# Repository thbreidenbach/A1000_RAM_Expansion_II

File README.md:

# A1000_RAM_Expansion_II
Modern Amiga 1000 Front Ram Expansion

This project is an effort to offer a modern appraoch to the Amiga 1000 front Ram Expansion.

The included PCB is untested as of now and will probably eithor not work or be subject to change after initial testing.
Thanks to Joachim Firnhaber for his help and good words (there's a lot of... potential), I would probably not have published the files without his okay.

I suggest Users wait until propper testing was done, before ordering boards.

Logic holds current **untested** code. Just like the PCB Design this is currently no more than a starting point or boilerplate. If you're adventurous and it works, leave me a message!!

**Back**

**Front**

The Board has Testpoints for RAM Glue-Logic so hopefully issues can be sorted out fast.
HTML BOM is included and should help sourcing parts. RAM should probably go with CY62128ELL Which is available in TSOP-32 Footprint at Reichelt at an extremely low price point. All Parts excluding the 60-Pin Connector are probably less than 20,-- EUR.

See License before ordering or going forward with this Design.

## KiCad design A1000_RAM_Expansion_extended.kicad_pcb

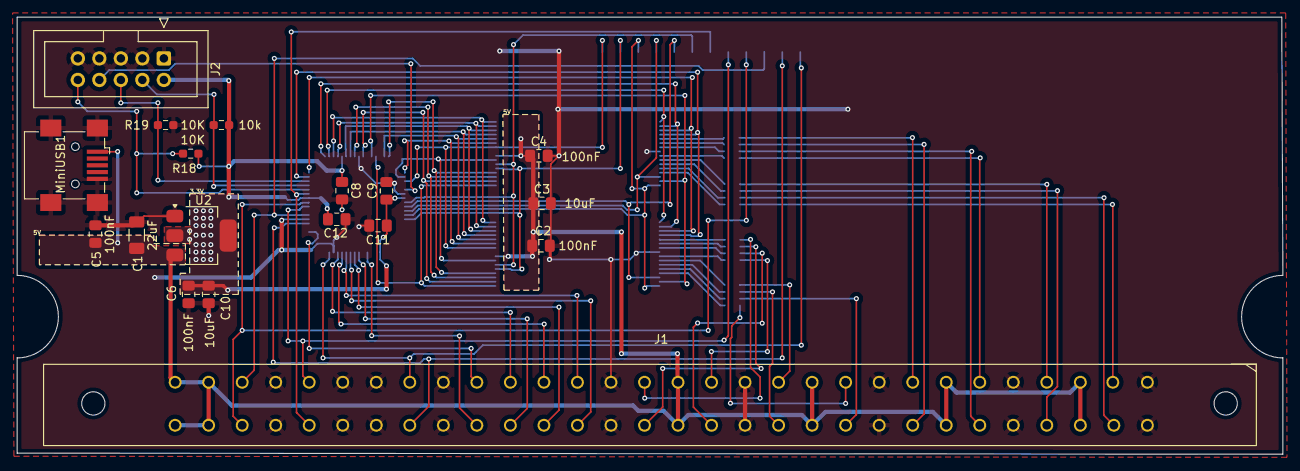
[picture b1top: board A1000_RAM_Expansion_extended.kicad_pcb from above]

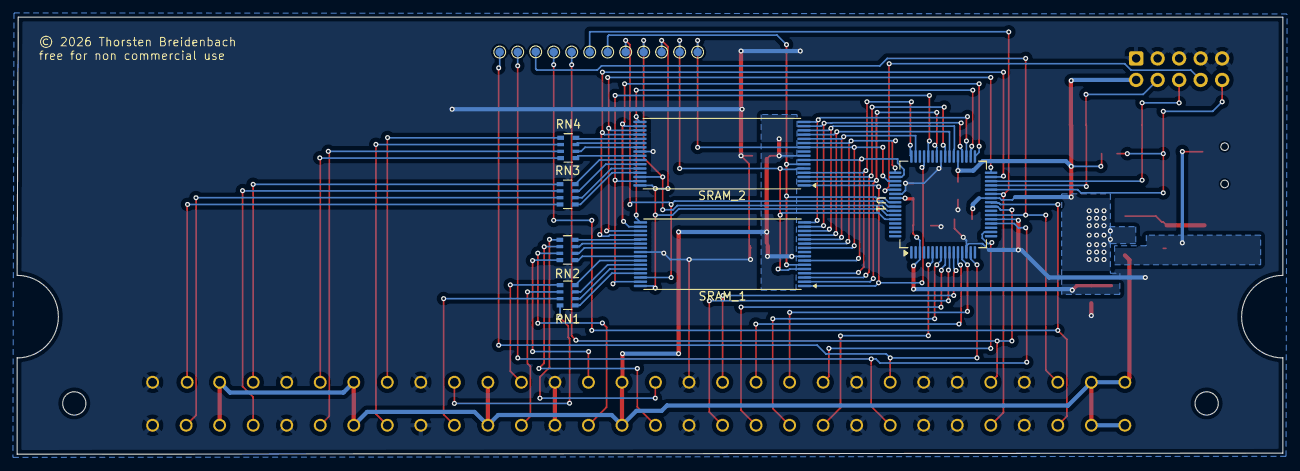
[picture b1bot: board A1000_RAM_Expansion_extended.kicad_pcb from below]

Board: 2 copper layers, 149.5 x 51.6 mm, 37 parts (19 on the bottom side), 75 nets.

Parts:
/casu_0, /casu_1: TestPoint_Pad_D1.0mm
/ce1_u: TestPoint_Pad_D1.0mm
/oe: TestPoint_Pad_D1.0mm
/ras: TestPoint_Pad_D1.0mm
/rrw: TestPoint_Pad_D1.0mm
/we: TestPoint_Pad_D1.0mm
C1: 22uF; C_1206_3216Metric_Pad1.33x1.80mm_HandSolder
C2, C5, C6, C8, C9, C11, C12: 100nF; C_0805_2012Metric_Pad1.18x1.45mm_HandSolder
C3, C10: 10uF; C_0805_2012Metric_Pad1.18x1.45mm_HandSolder
C4: C_Small; C_0805_2012Metric_Pad1.18x1.45mm_HandSolder
J1: Front_Connector; Connector_horizontal_amiga1.04_GREEN
J2: Conn_02x05_Odd_Even; IDC-Header_2x05_P2.54mm_Vertical
MiniUSB1: USB_Mini-B_Wuerth; USB_Mini-B_Wuerth_65100516121_Horizontal
R17: 10k; R_0603_1608Metric_Pad0.98x0.95mm_HandSolder
R18, R19: 10K; R_0603_1608Metric_Pad0.98x0.95mm_HandSolder
RN1, RN2, RN3, RN4: 33r; R_Array_Convex_4x0603
SRAM_1, SRAM_2: CY7C109D; TSOP-I-32_18.4x8mm_P0.5mm
U1: XC9572XL-xxVQx64; TQFP-64_10x10mm_P0.5mm
U2: LD1117S33TR_SOT223; SOT-223-3_TabPin2
casl0, casl1: TestPoint_Pad_D1.0mm
ce1_l, ce2: TestPoint_Pad_D1.0mm
sram_A16: TestPoint_Pad_D1.0mm

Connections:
+3.3V: C6.1, C8.1, C9.1, C10.1, C11.1, C12.1, J2.2, R17.2, R18.2, U1.3 (VCCINT), U1.26 (VCCIO), U1.37 (VCCINT), U1.55 (VCCIO), U2.2 (VO)
+5V: C1.1, C2.1, C3.1, C4.1, C5.1, J1.3, J1.7, J1.11, J1.15, J1.29, J1.30, J1.C (Pin_33), J1.H (Pin_37), J1.HH (Pin_59), J1.JJ (Pin_60), J1.M (Pin_41), J1.S (Pin_45), MiniUSB1.1 (VBUS), SRAM_1.8 (VCC), SRAM_2.8 (VCC), U2.3 (VI)
D0: J1.16, RN2.5 (R4.2)
D1: J1.T (Pin_46), RN2.6 (R3.2)
D2: J1.R (Pin_44), RN2.7 (R2.2)
D3: J1.14, RN2.8 (R1.2)
D4: J1.12, RN1.5 (R4.2)
D5: J1.N (Pin_42), RN1.6 (R3.2)
D6: J1.L (Pin_40), RN1.7 (R2.2)
D7: J1.10, RN1.8 (R1.2)
D8: J1.8, RN4.1 (R1.1)
D9: J1.J (Pin_38), RN4.2 (R2.1)
D10: J1.F (Pin_36), RN4.3 (R3.1)
D11: J1.6, RN4.4 (R4.1)
D12: J1.4, RN3.1 (R1.1)
D13: J1.D (Pin_34), RN3.2 (R2.1)
D14: J1.B (Pin_32), RN3.3 (R3.1)
D15: J1.2, RN3.4 (R4.1)
DRA0: J1.Y (Pin_51), U1.6 (I/O)
DRA1: J1.X (Pin_50), U1.8 (I/O)
DRA2: J1.W (Pin_49), U1.9 (I/O)
DRA3: J1.V (Pin_48), U1.10 (I/O)
DRA4: J1.18, U1.11 (I/O)
DRA5: J1.19, U1.12 (I/O)
DRA6: J1.20, U1.13 (I/O)
DRA7: J1.21, U1.18 (I/O)
GND: C1.2, C2.2, C3.2, C4.2, C5.2, C6.2, C8.2, C9.2, C10.2, C11.2, C12.2, J1.1, J1.5, J1.9, J1.13, J1.17, J1.22, J1.24, J1.25, J1.27, J1.A (Pin_31), J1.BB (Pin_54), J1.CC (Pin_55), J1.E (Pin_35), J1.EE, J1.K (Pin_39), J1.P (Pin_43), J1.U (Pin_47), J1.Z (Pin_52), J2.1, J2.3, J2.5, J2.7, J2.9, MiniUSB1.5 (GND), MiniUSB1.6 (Shield), R19.2, SRAM_1.24 (GND), SRAM_2.24 (GND), U1.14 (GND), U1.21 (GND), U1.41 (GND), U1.54 (GND), U2.1 (GND)
unnamed: RN1.1 (R1.1), SRAM_1.29 (I/O7)
unnamed: RN1.2 (R2.1), SRAM_1.28 (I/O6)
unnamed: RN1.3 (R3.1), SRAM_1.27 (I/O5)
unnamed: RN1.4 (R4.1), SRAM_1.26 (I/O4)
unnamed: RN2.1 (R1.1), SRAM_1.25 (I/O3)
unnamed: RN2.2 (R2.1), SRAM_1.23 (I/O2)
unnamed: RN2.3 (R3.1), SRAM_1.22 (I/O1)
unnamed: RN2.4 (R4.1), SRAM_1.21 (I/O0)
unnamed: RN3.8 (R1.2), SRAM_2.26 (I/O4)
unnamed: RN3.7 (R2.2), SRAM_2.27 (I/O5)
unnamed: RN3.6 (R3.2), SRAM_2.28 (I/O6)
unnamed: RN3.5 (R4.2), SRAM_2.29 (I/O7)
unnamed: RN4.8 (R1.2), SRAM_2.21 (I/O0)
unnamed: RN4.7 (R2.2), SRAM_2.22 (I/O1)
unnamed: RN4.6 (R3.2), SRAM_2.23 (I/O2)
unnamed: RN4.5 (R4.2), SRAM_2.25 (I/O3)
TCK: J2.6, R19.1, U1.30 (TCK)
TDI: J2.10, R18.1, U1.28 (TDI)
TDO: J2.8, U1.53 (TDO)
TMS: J2.4, R17.1, U1.29 (TMS)
ce2: SRAM_1.6 (CE2), SRAM_2.6 (CE2), U1.56 (I/O), ce2.7
sram_a0: SRAM_1.20 (A0), SRAM_2.20 (A0), U1.31 (I/O)
sram_a1: SRAM_1.19 (A1), SRAM_2.19 (A1), U1.32 (I/O)
sram_a2: SRAM_1.18 (A2), SRAM_2.18 (A2), U1.33 (I/O)
sram_a3: SRAM_1.17 (A3), SRAM_2.17 (A3), U1.34 (I/O)
sram_a4: SRAM_1.16 (A4), SRAM_2.16 (A4), U1.35 (I/O)
sram_a5: SRAM_1.15 (A5), SRAM_2.15 (A5), U1.36 (I/O)
sram_a6: SRAM_1.14 (A6), SRAM_2.14 (A6), U1.38 (I/O)
sram_a7: SRAM_1.13 (A7), SRAM_2.13 (A7), U1.39 (I/O)
sram_a8: SRAM_1.3 (A8), SRAM_2.3 (A8), U1.40 (I/O)
sram_a9: SRAM_1.2 (A9), SRAM_2.2 (A9), U1.42 (I/O)
sram_a10: SRAM_1.31 (A10), SRAM_2.31 (A10), U1.44 (I/O)
sram_a11: SRAM_1.1 (A11), SRAM_2.1 (A11), U1.45 (I/O)
sram_a12: SRAM_1.12 (A12), SRAM_2.12 (A12), U1.47 (I/O)
sram_a13: SRAM_1.4 (A13), SRAM_2.4 (A13), U1.48 (I/O)
sram_a14: SRAM_1.11 (A14), SRAM_2.11 (A14), U1.49 (I/O)
sram_a15: SRAM_1.7 (A15), SRAM_2.7 (A15), U1.50 (I/O)
sram_a16: SRAM_1.10 (A16), SRAM_2.10 (A16), U1.51 (I/O), sram_A16.12
/CASL0: J1.28, U1.22 (I/O), casl0.3
/CASL1: J1.FF (Pin_58), U1.25 (I/O), casl1.4
/CASU0: /casu_0.5, J1.26, U1.24 (I/O)
/CASU1: /casu_1.6, J1.DD (Pin_56), U1.27 (I/O)
/RAS: /ras.1, J1.23, U1.15 (I/O/GCK1)
/RRW: /rrw.2, J1.AA (Pin_53), U1.20 (I/O)
/ce1_l: SRAM_1.30 (_CE), U1.57 (I/O), ce1_l.8
/ce_1_u: /ce1_u.9, SRAM_2.30 (_CE), U1.58 (I/O)
/oe: /oe.10, SRAM_1.32 (_OE), SRAM_2.32 (_OE), U1.59 (I/O)
/we: /we.11, SRAM_1.5 (_WE), SRAM_2.5 (_WE), U1.60 (I/O)

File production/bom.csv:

Designator,Footprint,Quantity,Value,LCSC Part #
C1,1206,1,22uF,
"C10, C3",0805,2,10uF,
"C11, C12, C2, C5, C6, C8, C9",0805,7,100nF,
C4,0805,1,C_Small,
J1,Connector_horizontal_amiga1.04_GREEN,1,Front_Connector,
J2,IDC-Header_2x05_P2.54mm_Vertical,1,Conn_02x05_Odd_Even,
MINIUSB1,USB_Mini-B_Wuerth_65100516121_Horizontal,1,USB_Mini-B_Wuerth,
"R17, R18, R19",0603,3,10k,
"RN1, RN2, RN3, RN4",R_Array_Convex_4x0603,4,33r,
"SRAM_1, SRAM_2",TSOP-I-32_18.4x8mm_P0.5mm,2,CY7C109D,
U1,TQFP-64_10x10mm_P0.5mm,1,XC9572XL-xxVQx64,
U2,SOT-223-3_TabPin2,1,LD1117S33TR_SOT223,

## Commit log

2026-02-06 Logic files
2026-02-06 PCB Cleanup
2026-02-06 BOM and Production files refresh
2026-02-07 Cleanup
2026-02-08 Planes revised, gitignore
2026-02-08 Production FIles & BOM
2026-02-09 In da Zone..
2026-02-14 wrong Pin Association.. Bummer
2026-02-14 bad tmd switch in build

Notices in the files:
A1000_RAM_Expansion_extended.kicad_pcb:
© 2026 Thorsten Breidenbach
